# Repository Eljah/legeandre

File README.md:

# Лежандр / Спим с хаски

Мягкий напольный кокон для отдыха и работы с ноутбуком. Последняя CAD-конструкция — **R06**: камерная мягкая спинка без спинной рамы, локальная самостоятельная опора столика, переставляемый упор стоп и объёмное укрытие с отгибаемым клапаном клавиатуры.

## CAD опубликован

**[Открыть каталог CAD, моделей, PDF и рендеров](CAD_INDEX.md)**

В ветке `sync/r01-r06-20261002` находятся 23 STEP-сборки R01/R02/R04/R05/R06, исходники CadQuery, геометрические данные и виды. GitHub Actions добавил недостающие CAD-материалы обычными файлами и повторно открыл все сборки. `main` пока не изменён.

[Рабочая модель R06](revisions/R06/cad/Lezhandr_R06_folded.step) · [Разрез с человеком](revisions/R06/cad/Lezhandr_R06_occupied_interior.step) · [PDF-альбом R06](revisions/R06/docs/Lezhandr_R06_CAD_review.pdf)

## Состав проекта

| Компонент | Каталог |
|---|---|
| CAD и документация последней конструкции | [revisions/R06](revisions/R06/) |
| Предыдущие конструкции | [R01](revisions/R01/), [R02](revisions/R02/), [R04](revisions/R04/), [R05](revisions/R05/) |
| Электроника, прошивка и Java-приложения предыдущей версии | [revisions/R02](revisions/R02/) |
| Вышивка: DST, EXP, объектные данные | [revisions/R03](revisions/R03/) |
| Проверки происхождения и передачи | [provenance](provenance/) |

## Статус передачи

CAD-публикация проверена: [отчёт Actions](provenance/CAD_PUBLISH_VERIFICATION.json). Из него видны точные файлы, контрольные суммы и пределы проверки. Полную передачу всех исторических вложений разговора этот статус не утверждает; подробности — [TRANSFER_STATUS.md](TRANSFER_STATUS.md).

Материалы размещены распакованными. Для работы не требуется загружать дополнительный архив в стороннее хранилище или запускать локальный скрипт дозагрузки.

## Ограничения инженерной модели

Проект не прошёл физическое изготовление и проверку безопасности. Не завершены расчёт гранулярного наполнителя, измерение контактных давлений, полный производственный раскрой, испытания тепловой и электрической части. Геометрические сценарии посадки не являются подтверждённой эргономикой.

Механика R06, вышивка R03 и электроника/ПО R02 не образуют заново испытанную интегрированную версию. Отсутствие нагревателя рук в CAD не отключает прежний четвёртый канал прошивки. Нагрев во сне и использование прототипа под напряжением с человеком не разрешаются этой документацией. Столик не является поручнем.

Первоначальный README сохранён в [provenance/ORIGINAL_REPOSITORY_README.md](provenance/ORIGINAL_REPOSITORY_README.md).

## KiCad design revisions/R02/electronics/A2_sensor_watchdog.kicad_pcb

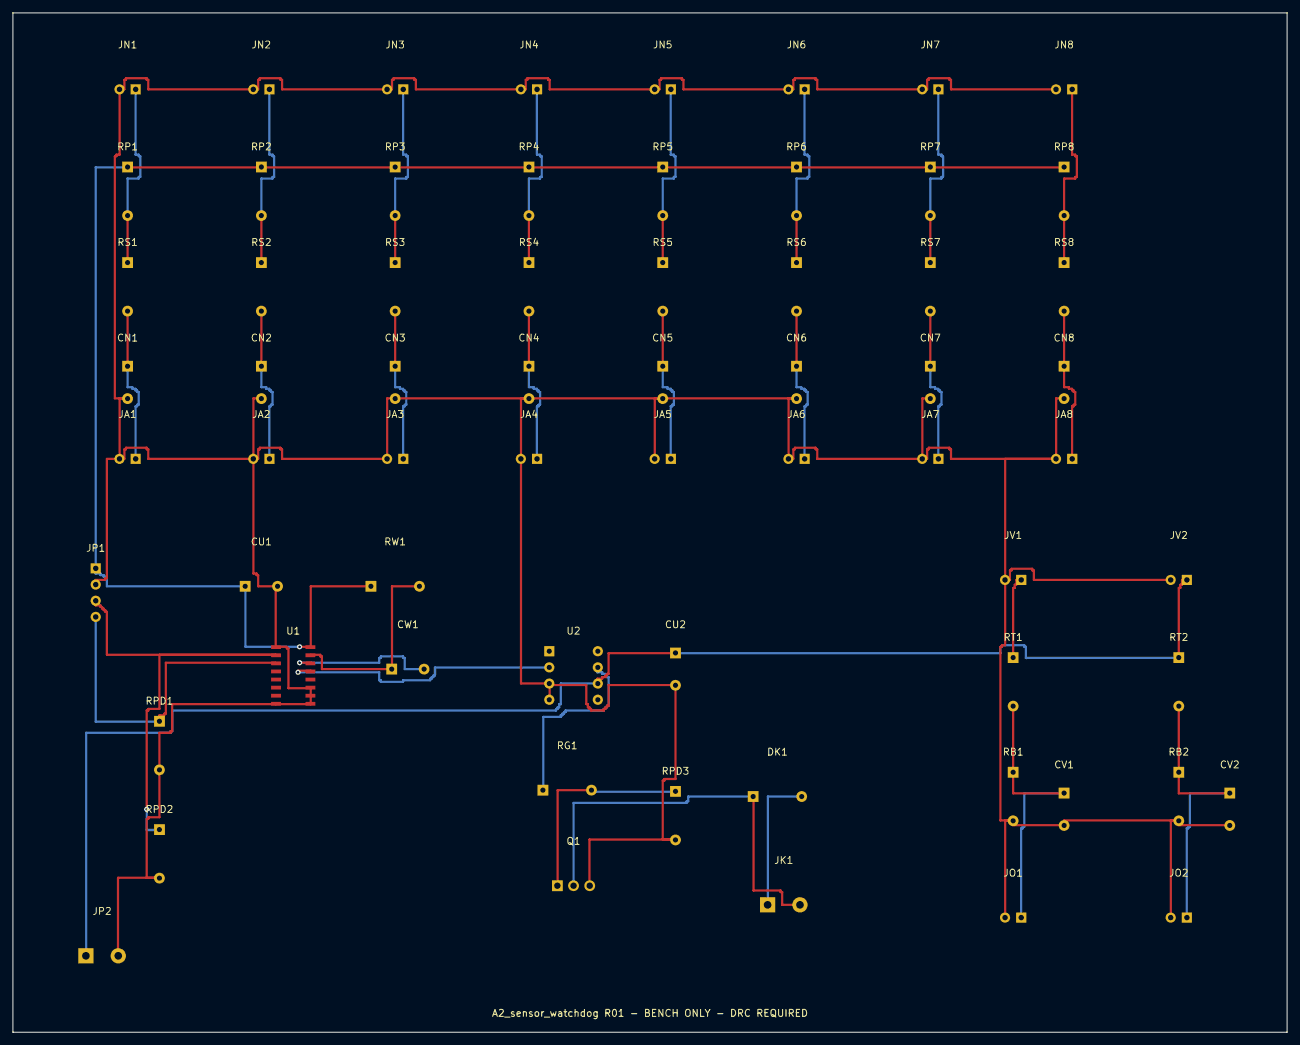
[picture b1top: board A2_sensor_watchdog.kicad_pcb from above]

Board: 2 copper layers, 200.0 x 160.0 mm, 65 parts (0 on the bottom side), 31 nets.

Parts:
CN1, CN2, CN3, CN4, CN5, CN6, CN7, CN8: 100n; Husky_C_2
CU1, CU2: 100n; Husky_C_2
CV1, CV2: 100n; Husky_C_2
CW1: 2.2u low leakage; Husky_C_2
DK1: 1N4007 A=1 K=2; Husky_R_2
JA1: ESP ADC 0; Husky_HEADER_2
JA2: ESP ADC 1; Husky_HEADER_2
JA3: ESP ADC 2; Husky_HEADER_2
JA4: ESP ADC 3; Husky_HEADER_2
JA5: ESP ADC 4; Husky_HEADER_2
JA6: ESP ADC 5; Husky_HEADER_2
JA7: ESP ADC 6; Husky_HEADER_2
JA8: ESP ADC 7; Husky_HEADER_2
JK1: External K1 coil after NC chain; Husky_TERM_2
JN1, JN2, JN3, JN4, JN5, JN6, JN7, JN8: 10k B3950 NTC; Husky_HEADER_2
JO1, JO2: ESP voltage ADC / GND; Husky_HEADER_2
JP1: 3V3 / GND / WD / PERMIT; Husky_HEADER_4
JP2: RAW12 / GND; Husky_TERM_2
JV1, JV2: Sense IN / GND; Husky_HEADER_2
Q1: STP55NF06L; Husky_TO220_3
RB1, RB2: 10k 1%; Husky_R_2
RG1: 47R; Husky_R_2
RP1, RP2, RP3, RP4, RP5, RP6, RP7, RP8: 10k 1%; Husky_R_2
RPD1, RPD2, RPD3: 100k; Husky_R_2
RS1, RS2, RS3, RS4, RS5, RS6, RS7, RS8: 100R; Husky_R_2
RT1: 100k 1%; Husky_R_2
RT2: 47k 1%; Husky_R_2
RW1: 470k 1%; Husky_R_2
U1: 74HC123D SO16; Husky_SO16_16
U2: TC4427EPA; Husky_DIP8_8

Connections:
3V3: CU1.1, JP1.1, RP1.1, RP2.1, RP3.1, RP4.1, RP5.1, RP6.1, RP7.1, RP8.1, RW1.1, U1.16
ADC0: CN1.1, JA1.1, RS1.2
ADC1: CN2.1, JA2.1, RS2.2
ADC2: CN3.1, JA3.1, RS3.2
ADC3: CN4.1, JA4.1, RS4.2
ADC4: CN5.1, JA5.1, RS5.2
ADC5: CN6.1, JA6.1, RS6.2
ADC6: CN7.1, JA7.1, RS7.2
ADC7: CN8.1, JA8.1, RS8.2
BAT24: JV1.1, RT1.1
BAT_ADC: CV1.1, JO1.1, RB1.1, RT1.2
CEXT: CW1.2, U1.14
COIL_MINUS: DK1.1, JK1.2, Q1.2
COIL_PLUS: DK1.2, JK1.1
GND: CN1.2, CN2.2, CN3.2, CN4.2, CN5.2, CN6.2, CN7.2, CN8.2, CU1.2, CU2.2, CV1.2, CV2.2, JA1.2, JA2.2, JA3.2, JA4.2, JA5.2, JA6.2, JA7.2, JA8.2, JN1.2, JN2.2, JN3.2, JN4.2, JN5.2, JN6.2, JN7.2, JN8.2, JO1.2, JO2.2, JP1.2, JP2.2, JV1.2, JV2.2, Q1.3, RB1.2, RB2.2, RPD1.2, RPD2.2, RPD3.2, U1.1, U1.8, U1.9, U1.10, U1.11, U2.3, U2.4
H12_ADC: CV2.1, JO2.1, RB2.1, RT2.2
NTC0: JN1.1, RP1.2, RS1.1
NTC1: JN2.1, RP2.2, RS2.1
NTC2: JN3.1, RP3.2, RS3.1
NTC3: JN4.1, RP4.2, RS4.1
NTC4: JN5.1, RP5.2, RS5.1
NTC5: JN6.1, RP6.2, RS6.1
NTC6: JN7.1, RP7.2, RS7.1
NTC7: JN8.1, RP8.2, RS8.1
PERMIT: JP1.4, RPD1.1, U1.3
RAW12: CU2.1, JP2.1, JV2.1, RT2.1, U2.6
RCEXT: CW1.1, RW1.2, U1.15
RELAY_DRIVE: RG1.1, U2.7
RELAY_GATE: Q1.1, RG1.2, RPD3.1
WD: JP1.3, RPD2.1, U1.2
WD_OK: U1.13, U2.2

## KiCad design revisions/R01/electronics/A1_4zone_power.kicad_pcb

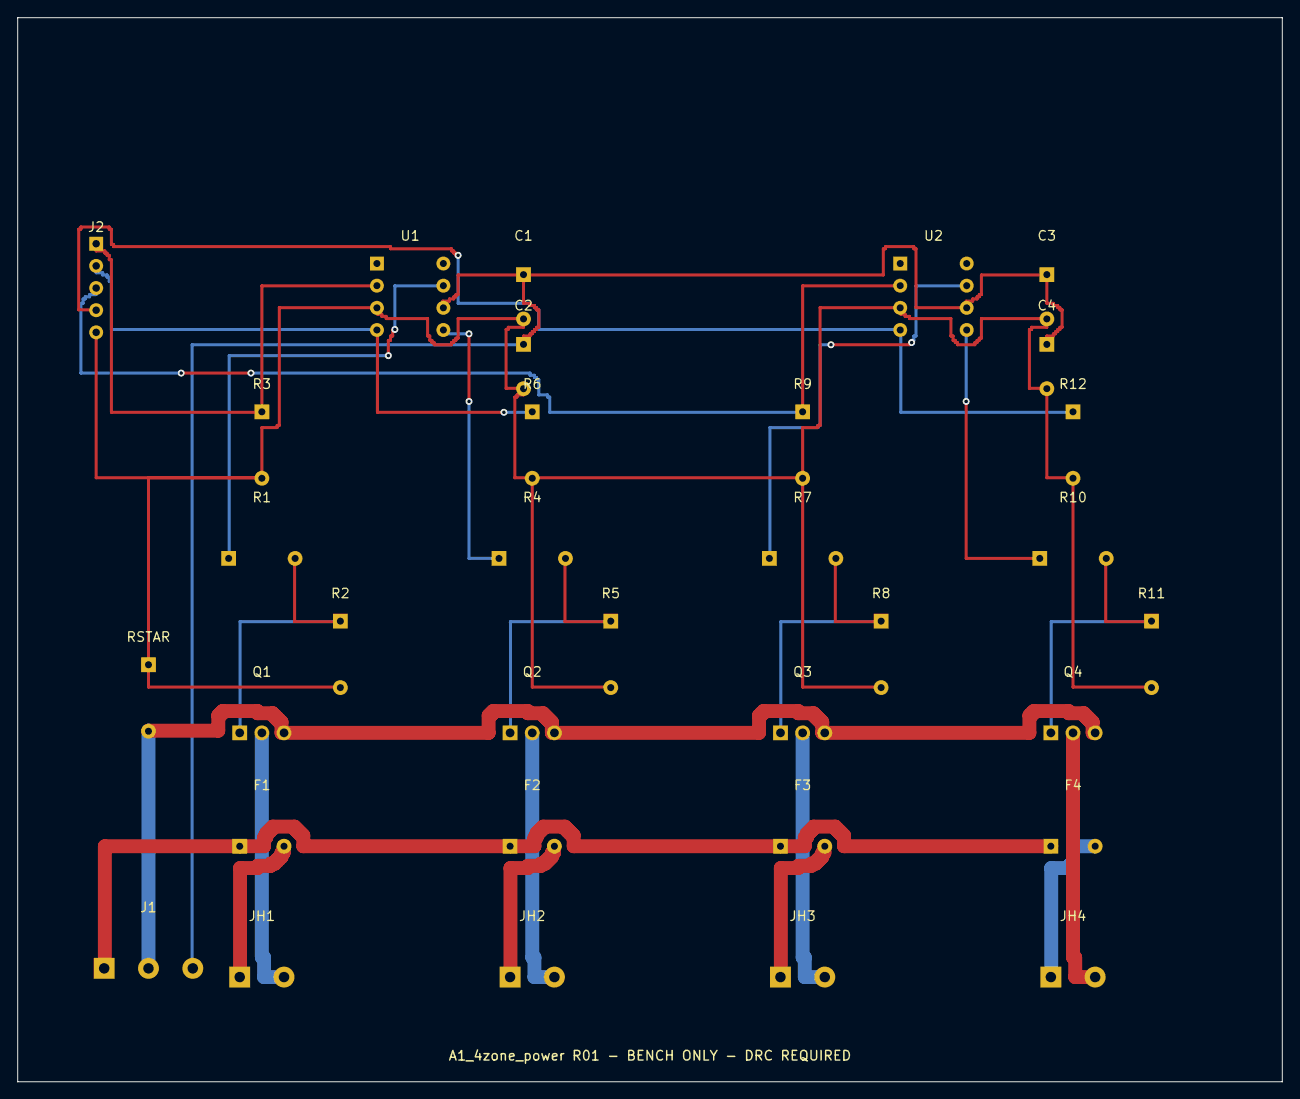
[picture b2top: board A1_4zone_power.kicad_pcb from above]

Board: 2 copper layers, 145.0 x 122.0 mm, 33 parts (0 on the bottom side), 24 nets.

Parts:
C1, C3: 100n / 50V; Husky_C_2
C2, C4: 10u / 25V; Husky_C_2
F1, F2: 2.5A DC fuse - footprint VERIFY; Husky_C_2
F3: 1.6A DC fuse - footprint VERIFY; Husky_C_2
F4: 1.0A DC fuse - footprint VERIFY; Husky_C_2
J1: 12V: SAFE / GND / RAW; Husky_TERM_3
J2: PWM0..3 / GND; Husky_HEADER_5
JH1: Heater Z0; Husky_TERM_2
JH2: Heater Z1; Husky_TERM_2
JH3: Heater Z2; Husky_TERM_2
JH4: Heater Z3; Husky_TERM_2
Q1, Q2, Q3, Q4: STP55NF06L; Husky_TO220_3
R1, R4, R7, R10: 47R; Husky_R_2
R2, R5, R8, R11: 100k gate pulldown; Husky_R_2
R3, R6, R9, R12: 10k input pulldown; Husky_R_2
RSTAR: 0R logic/power star; Husky_R_2
U1, U2: TC4427EPA; Husky_DIP8_8

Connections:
DRAIN0: JH1.2, Q1.2
DRAIN1: JH2.2, Q2.2
DRAIN2: JH3.2, Q3.2
DRAIN3: JH4.2, Q4.2
DRIVE0: R1.1, U1.7
DRIVE1: R4.1, U1.5
DRIVE2: R7.1, U2.7
DRIVE3: R10.1, U2.5
GATE0: Q1.1, R1.2, R2.1
GATE1: Q2.1, R4.2, R5.1
GATE2: Q3.1, R7.2, R8.1
GATE3: Q4.1, R10.2, R11.1
GND: C1.2, C2.2, C3.2, C4.2, J2.5, R2.2, R3.2, R5.2, R6.2, R8.2, R9.2, R11.2, R12.2, RSTAR.1, U1.3, U2.3
H12: F1.1, F2.1, F3.1, F4.1, J1.1
HEAT0: F1.2, JH1.1
HEAT1: F2.2, JH2.1
HEAT2: F3.2, JH3.1
HEAT3: F4.2, JH4.1
PGND: J1.2, Q1.3, Q2.3, Q3.3, Q4.3, RSTAR.2
PWM0: J2.1, R3.1, U1.2
PWM1: J2.2, R6.1, U1.4
PWM2: J2.3, R9.1, U2.2
PWM3: J2.4, R12.1, U2.4
RAW12: C1.1, C2.1, C3.1, C4.1, J1.3, U1.6, U2.6

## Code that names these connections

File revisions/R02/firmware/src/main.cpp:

/* R01 BENCH FIRMWARE ONLY. Physical thermostat/relay/watchdog chain required.
 * Never use software limits as the sole protection for a person.
 */
#include <Arduino.h>
#include <BLEDevice.h>
#include <BLEServer.h>
#include <BLEUtils.h>
#include <BLE2902.h>
#include <BLESecurity.h>
#include <esp_task_wdt.h>
#include <esp_arduino_version.h>
#include "ControlCore.hpp"
using namespace husky;
constexpr int NTC[8]={1,2,4,5,6,7,8,9},PWM[4]={12,13,14,15};
constexpr int BAT_ADC=10,H12_ADC=11,ARM=16,FOLD=17,WET=18,LOOP=21,PERMIT=40,WD=41;
constexpr char SERVICE[]="f8720001-7649-4a9f-bd4e-11ee30c01001";
constexpr char RX[]="f8720002-7649-4a9f-bd4e-11ee30c01001";
constexpr char TX[]="f8720003-7649-4a9f-bd4e-11ee30c01001";
Controller ctl; Input input; BLECharacteristic* tx=nullptr;
volatile bool authenticated=false,connected=false;volatile uint32_t pairUntil=0;
uint32_t passkey=0; QueueHandle_t commands;
struct Command{char text[81];};
// BLE callbacks only enqueue; controller state belongs to the main task.
class Rx: public BLECharacteristicCallbacks{
 void onWrite(BLECharacteristic* ch)override{
  if(!authenticated)return;auto v=ch->getValue();const char* p=v.c_str();
  size_t n=std::strlen(p);if(!n||n>80)return;
  Command c{};std::memcpy(c.text,p,n);while(n&&(c.text[n-1]=='\n'||c.text[n-1]=='\r'))c.text[--n]=0;
  xQueueSend(commands,&c,0);
 }
};
class Server:public BLEServerCallbacks{
 void onConnect(BLEServer*)override{connected=true;authenticated=false;}
 void onDisconnect(BLEServer*)override{connected=false;authenticated=false;BLEDevice::startAdvertising();}
};
class Security:public BLESecurityCallbacks{
 uint32_t onPassKeyRequest()override{return passkey;}
 void onPassKeyNotify(uint32_t n)override{Serial.printf("DBG PAIR PIN %06lu\n",(unsigned long)n);}
 bool onConfirmPIN(uint32_t)override{return false;}
 bool onSecurityRequest()override{return int32_t(pairUntil-millis())>0;}
 void onAuthenticationComplete(esp_ble_auth_cmpl_t c)override{authenticated=c.success;}
};
float ntc(int pin){
 // Divider: 3.3 V -- 10k 1% -- ADC -- 10k B3950 NTC -- GND.
 float mv=0;for(int i=0;i<8;i++)mv+=analogReadMilliVolts(pin);mv/=8;
 if(mv<80||mv>3050)return NAN; // open/short and rail clipping fail closed
 const float r=10000.0f*mv/(3300.0f-mv);
 return 1.0f/(1.0f/298.15f+logf(r/10000.0f)/3950.0f)-273.15f;
}
void outputs(){
 bool enable=ctl.output().relay;
 // Drop common permit before changing gates on a fault.
 if(!enable)digitalWrite(PERMIT,LOW);
 for(int z=0;z<4;z++){
  uint32_t duty=enable?uint32_t(ctl.output().duty[z]*1023):0;
#if ESP_ARDUINO_VERSION_MAJOR >= 3
  ledcWrite(PWM[z],duty);
#else
  ledcWrite(z,duty);
#endif
 }
 if(enable)digitalWrite(PERMIT,HIGH);
}
void setup(){
 pinMode(PERMIT,OUTPUT);digitalWrite(PERMIT,LOW);pinMode(WD,OUTPUT);digitalWrite(WD,LOW);
 for(int z=0;z<4;z++){
  pinMode(PWM[z],OUTPUT);digitalWrite(PWM[z],LOW);
#if ESP_ARDUINO_VERSION_MAJOR >= 3
  ledcAttach(PWM[z],1000,10);ledcWrite(PWM[z],0);
#else
  ledcSetup(z,1000,10);ledcAttachPin(PWM[z],z);ledcWrite(z,0);
#endif
 }
 Serial.begin(115200);analogReadResolution(12);analogSetAttenuation(ADC_11db);
 for(int p:{ARM,FOLD,WET,LOOP})pinMode(p,INPUT_PULLUP);
 commands=xQueueCreate(8,sizeof(Command));
 passkey=100000+(uint32_t(ESP.getEfuseMac()>>16)%900000); // prototype unique printed PIN; not a production secret
 BLEDevice::init("Husky-Lezhandr-R01");BLEDevice::setEncryptionLevel(ESP_BLE_SEC_ENCRYPT_MITM);
 BLEDevice::setSecurityCallbacks(new Security());
 auto sec=new BLESecurity();sec->setAuthenticationMode(ESP_LE_AUTH_REQ_SC_MITM_BOND);
 sec->setCapability(ESP_IO_CAP_OUT);sec->setStaticPIN(passkey);
 auto server=BLEDevice::createServer();server->setCallbacks(new Server());auto svc=server->createService(SERVICE);
 auto rx=svc->createCharacteristic(RX,BLECharacteristic::PROPERTY_WRITE);
 rx->setAccessPermissions(ESP_GATT_PERM_WRITE_ENC_MITM);rx->setCallbacks(new Rx());
 tx=svc->createCharacteristic(TX,BLECharacteristic::PROPERTY_NOTIFY|BLECharacteristic::PROPERTY_READ);
 tx->setAccessPermissions(ESP_GATT_PERM_READ_ENC_MITM);tx->addDescriptor(new BLE2902());
 svc->start();BLEDevice::getAdvertising()->addServiceUUID(SERVICE);BLEDevice::startAdvertising();
#if ESP_ARDUINO_VERSION_MAJOR >= 3
 esp_task_wdt_config_t cfg={.timeout_ms=2000,.idle_core_mask=0,.trigger_panic=true};esp_task_wdt_init(&cfg);
#else
 esp_task_wdt_init(2,true);
#endif
 esp_task_wdt_add(nullptr);
 Serial.println("DBG R01 BENCH ONLY. Hold physical ARM for 2 seconds; outputs remain OFF until START.");
}
void loop(){
 static uint32_t prev=0,report=0,press=0;static bool wasPressed=false,acted=false,beat=false;
 static char serial[81];static size_t used=0;static bool discard=false;
 uint32_t now=millis();
 while(Serial.available()){
  char c=char(Serial.read());
  if(c=='\r')continue;
  if(c=='\n'){if(!discard&&used){serial[used]=0;ctl.command(serial,input,now);}used=0;discard=false;}
  else if(!discard){if(used<80)serial[used++]=c;else{discard=true;used=0;}}
 }
 Command cmd{};while(xQueueReceive(commands,&cmd,0)==pdTRUE)ctl.command(cmd.text,input,now);
 if(uint32_t(now-prev)<100){delay(2);return;}prev=now;
 for(int i=0;i<8;i++)input.c[i]=ntc(NTC[i]);
 input.batteryV=analogReadMilliVolts(BAT_ADC)*11.0f/1000.0f; // 100k / 10k divider
 input.heaterV=analogReadMilliVolts(H12_ADC)*5.7f/1000.0f;  // 47k / 10k divider
 input.deployed=digitalRead(FOLD)==LOW;input.dry=digitalRead(WET)==LOW;input.safetyLoop=digitalRead(LOOP)==LOW;
 input.sampledMs=now;
 bool pressed=digitalRead(ARM)==LOW;
 if(pressed&&!wasPressed){press=now;acted=false;}
 if(pressed&&!acted&&uint32_t(now-press)>2000){
  acted=true;if(ctl.localArm(input,now)){pairUntil=now+60000;Serial.printf("DBG LOCAL ARM; PAIR PIN %06lu\n",(unsigned long)passkey);}
 }
 wasPressed=pressed;ctl.step(input,now);outputs();
 // Heartbeat generated here, NOT by a timer ISR. A stalled control task must stop the external watchdog.
 beat=!beat;digitalWrite(WD,beat);esp_task_wdt_reset();
 if(uint32_t(now-report)>=1000){
  report=now;char status[192];ctl.status(status,sizeof status,input);Serial.print(status);
  if(connected&&authenticated){ // 20-byte notification chunks work even before an MTU exchange.
   size_t n=std::strlen(status);for(size_t i=0;i<n;i+=20){tx->setValue((uint8_t*)status+i,std::min(size_t(20),n-i));tx->notify();delay(3);}
  }
 }
}
